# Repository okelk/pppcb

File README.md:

# pppcb

Sensor pcb for makersxchange Project 2021.

PPPCB is a ESP8266 development board with an integrated LED-Matrix and Piezo Preamplifier.

The board us currently still UNTESTED (as of 2021-02-25)

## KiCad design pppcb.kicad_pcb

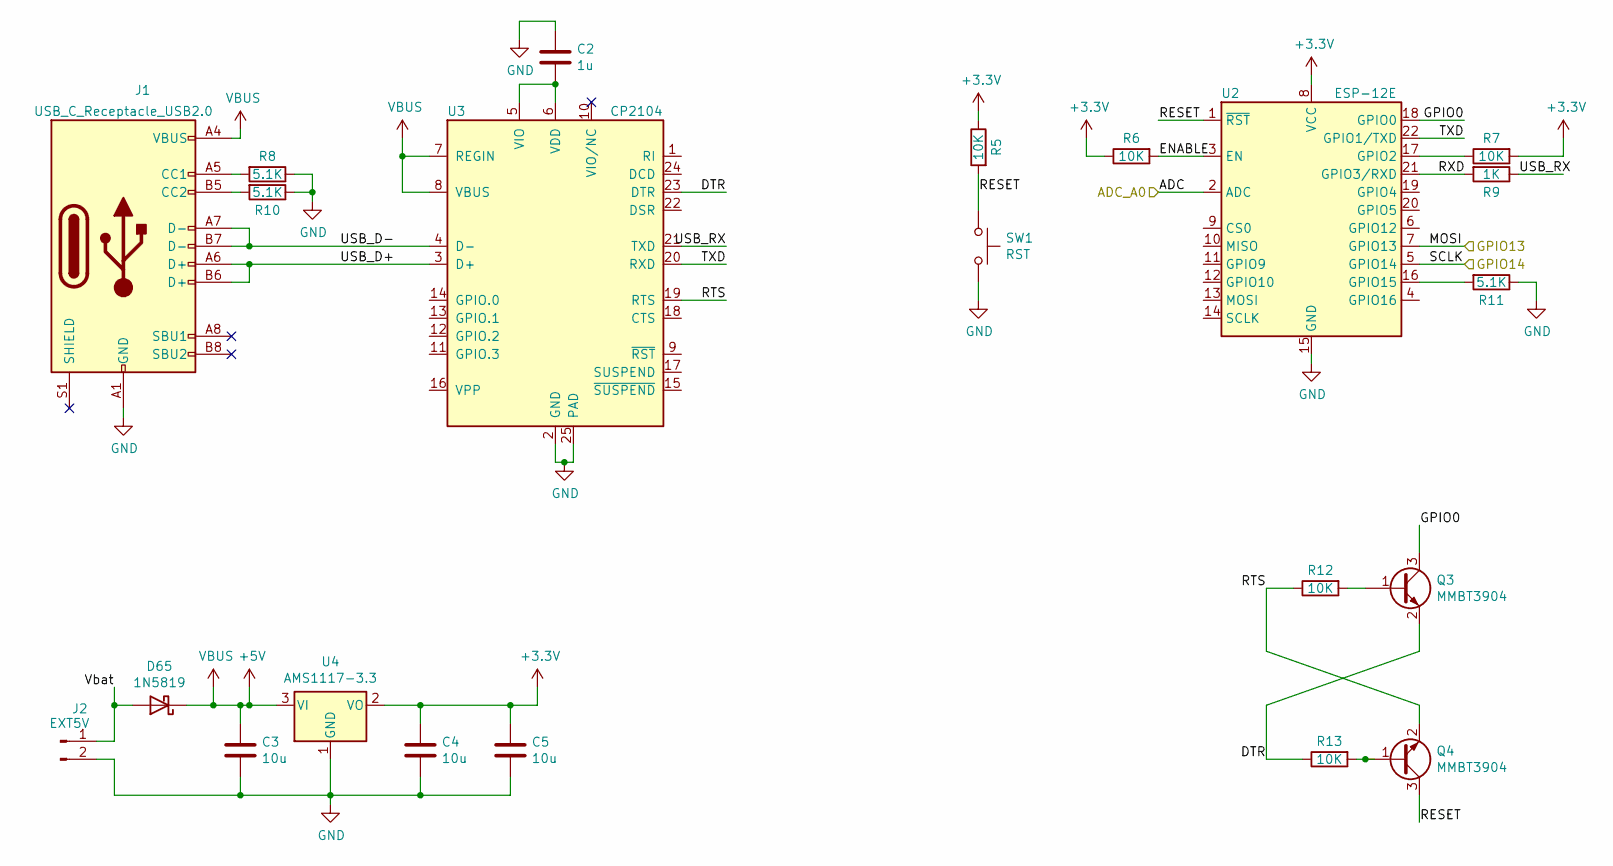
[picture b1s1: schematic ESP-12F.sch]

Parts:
C2: 1u; C_0603_1608Metric_Pad1.08x0.95mm_HandSolder
C3, C4, C5: 10u; C_0805_2012Metric
D65: 1N5819; D_DO-41_SOD81_P10.16mm_Horizontal
J1: USB_C_Receptacle_USB2.0; USB_C_Receptacle_HRO_TYPE-C-31-M-12
J2: EXT5V; PinHeader_1x02_P2.54mm_Horizontal
Q3, Q4: MMBT3904; SOT-23
R5, R6, R7, R12, R13: 10K; R_0603_1608Metric_Pad0.98x0.95mm_HandSolder
R8, R10, R11: 5.1K; R_0603_1608Metric_Pad0.98x0.95mm_HandSolder
R9: 1K; R_0603_1608Metric_Pad0.98x0.95mm_HandSolder
SW1: RST; Button_Tact_Sqkg
U2: ESP-12E
U3: CP2104; QFN-24-1EP_4x4mm_P0.5mm_EP2.6x2.6mm
U4: AMS1117-3.3; SOT-223-3_TabPin2

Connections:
+5V: C3.1, D65.1 (K), J1.A4 (VBUS), J1.A9 (VBUS), J1.B4 (VBUS), J1.B9 (VBUS), U3.7 (REGIN), U3.8 (VBUS), U4.3 (VI); also elsewhere on the board
/ESP-12F/ADC_A0: U2.2 (ADC); also elsewhere on the board
/ESP-12F/DTR: Q3.2 (E), R13.1, U3.23 (DTR)
/ESP-12F/ENABLE: R6.2, U2.3 (EN)
/ESP-12F/GPIO0: Q3.3 (C), U2.18 (GPIO0)
/ESP-12F/GPIO13: U2.7 (GPIO13); also elsewhere on the board
/ESP-12F/GPIO14: U2.5 (GPIO14); also elsewhere on the board
/ESP-12F/RESET: Q4.3 (C), R5.2, SW1.1, U2.1 (~RST)
/ESP-12F/RTS: Q4.2 (E), R12.1, U3.19 (RTS)
/ESP-12F/RXD: R9.2, U2.21 (GPIO3/RXD)
/ESP-12F/TXD: U2.22 (GPIO1/TXD), U3.20 (RXD)
/ESP-12F/USB_D+: J1.A6 (D+), J1.B6 (D+), U3.3 (D+)
/ESP-12F/USB_D-: J1.A7 (D-), J1.B7 (D-), U3.4 (D-)
/ESP-12F/USB_RX: R9.1, U3.21 (TXD)
/ESP-12F/Vbat: D65.2 (A), J2.1
GND: C2.1, C3.2, C4.2, C5.2, J1.A1 (GND), J1.A12 (GND), J1.B1 (GND), J1.B12 (GND), J2.2, R8.1, R10.1, R11.1, SW1.2, U2.15 (GND), U3.2 (GND), U3.25 (PAD), U4.1 (GND); also elsewhere on the board
unnamed: C2.2, U3.5 (VIO), U3.6 (VDD)
unnamed: J1.A5 (CC1), R8.2
unnamed: J1.B5 (CC2), R10.2
unnamed: Q3.1 (B), R12.2
unnamed: Q4.1 (B), R13.2
unnamed: R7.1, U2.17 (GPIO2)
unnamed: R11.2, U2.16 (GPIO15)

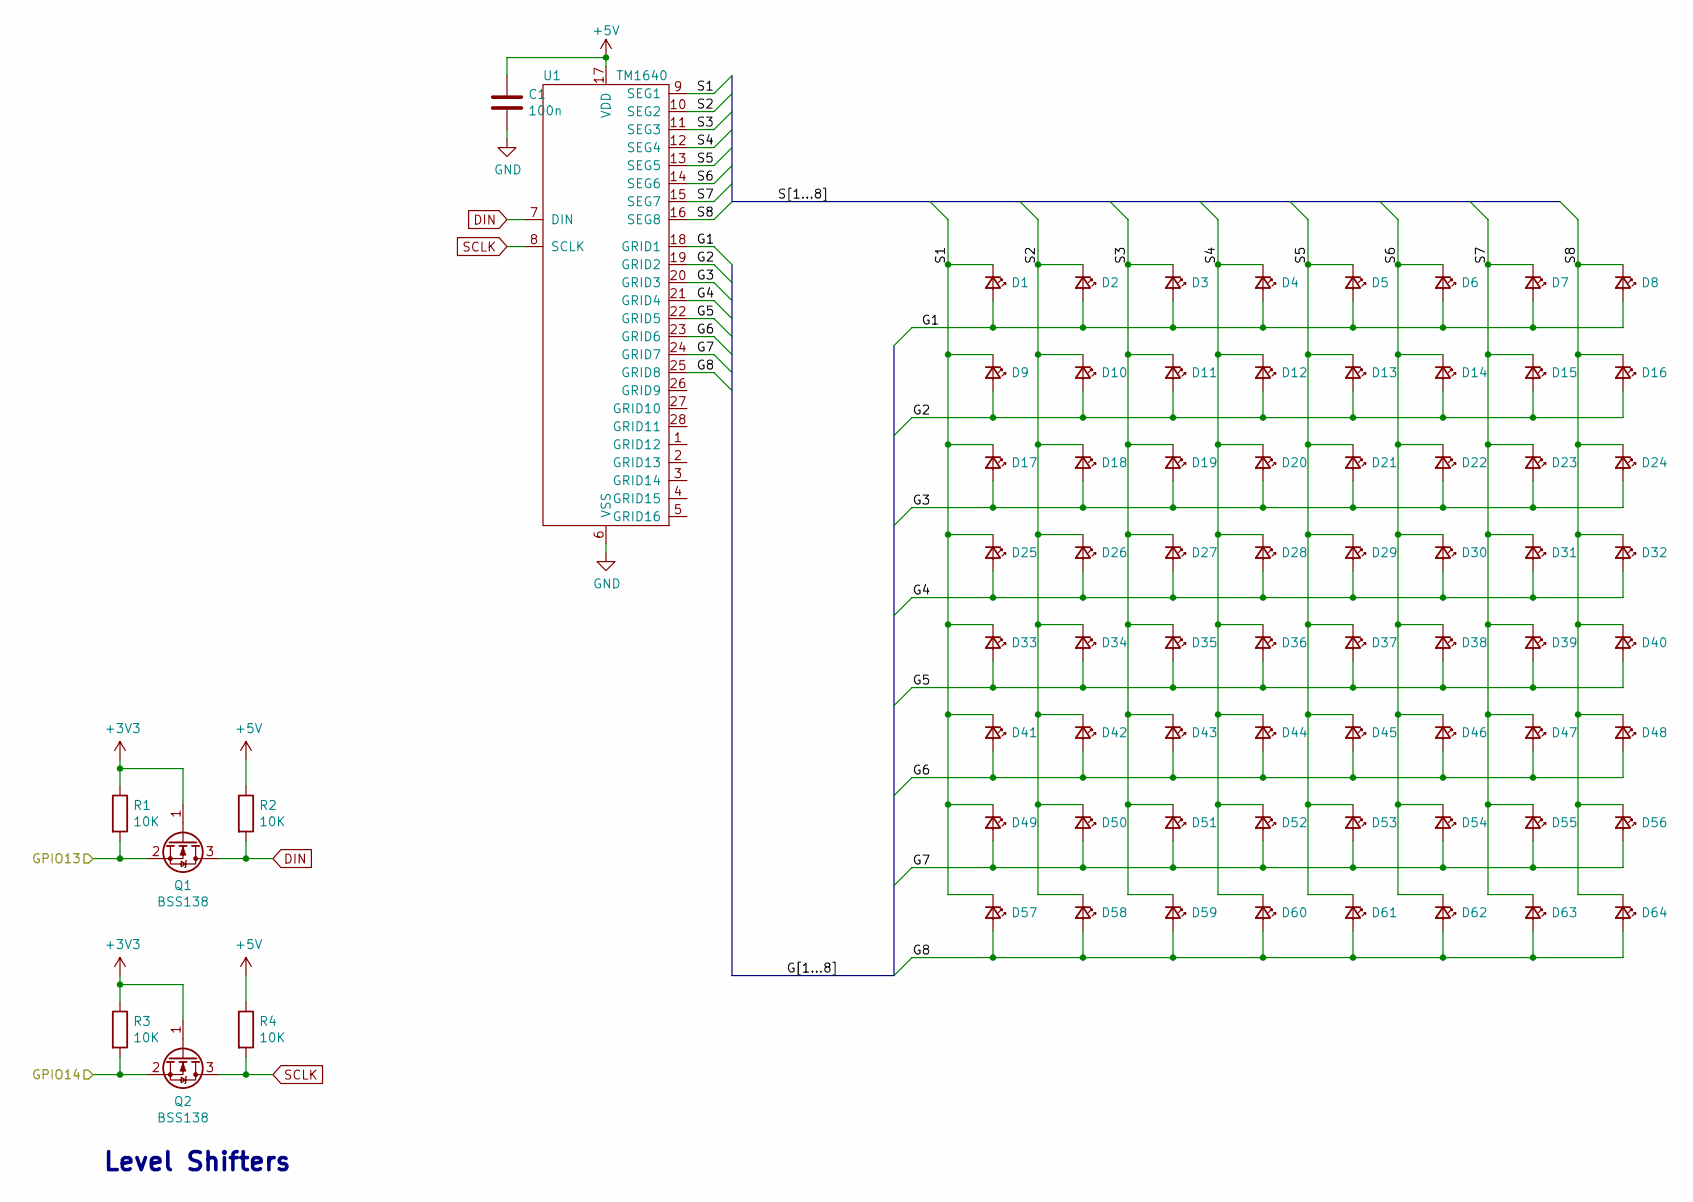
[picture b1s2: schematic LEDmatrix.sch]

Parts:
C1: 100n; C_0603_1608Metric_Pad1.08x0.95mm_HandSolder
D1, D2, D3, D4, D5, D6, D7, D8, D9, D10, D11, D12, D13, D14, D15, D16, D17, D18, D19, D20, D21, D22, D23, D24, D25, D26, D27, D28, D29, D30, D31, D32, D33, D34, D35, D36, D37, D38, D39, D40, D41, D42, D43, D44, D45, D46, D47, D48, D49, D50, D51, D52, D53, D54, D55, D56, D57, D58, D59, D60, D61, D62, D63, D64: LED_Small; LED_0603_1608Metric_Pad1.05x0.95mm_HandSolder
Q1, Q2: BSS138; SOT-23
R1, R2, R3, R4: 10K; R_0603_1608Metric_Pad0.98x0.95mm_HandSolder
U1: TM1640; SOIC-28W_7.5x18.7mm_P1.27mm

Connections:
+5V: C1.1, R2.1, R4.1, U1.17 (VDD); also elsewhere on the board
/ESP-12F/GPIO13: Q1.2 (S), R1.2; also elsewhere on the board
/ESP-12F/GPIO14: Q2.2 (S), R3.2; also elsewhere on the board
/LEDmatrix/G1: D1.2 (A), D2.2 (A), D3.2 (A), D4.2 (A), D5.2 (A), D6.2 (A), D7.2 (A), D8.2 (A), U1.18 (GRID1)
/LEDmatrix/G2: D9.2 (A), D10.2 (A), D11.2 (A), D12.2 (A), D13.2 (A), D14.2 (A), D15.2 (A), D16.2 (A), U1.19 (GRID2)
/LEDmatrix/G3: D17.2 (A), D18.2 (A), D19.2 (A), D20.2 (A), D21.2 (A), D22.2 (A), D23.2 (A), D24.2 (A), U1.20 (GRID3)
/LEDmatrix/G4: D25.2 (A), D26.2 (A), D27.2 (A), D28.2 (A), D29.2 (A), D30.2 (A), D31.2 (A), D32.2 (A), U1.21 (GRID4)
/LEDmatrix/G5: D33.2 (A), D34.2 (A), D35.2 (A), D36.2 (A), D37.2 (A), D38.2 (A), D39.2 (A), D40.2 (A), U1.22 (GRID5)
/LEDmatrix/G6: D41.2 (A), D42.2 (A), D43.2 (A), D44.2 (A), D45.2 (A), D46.2 (A), D47.2 (A), D48.2 (A), U1.23 (GRID6)
/LEDmatrix/G7: D49.2 (A), D50.2 (A), D51.2 (A), D52.2 (A), D53.2 (A), D54.2 (A), D55.2 (A), D56.2 (A), U1.24 (GRID7)
/LEDmatrix/G8: D57.2 (A), D58.2 (A), D59.2 (A), D60.2 (A), D61.2 (A), D62.2 (A), D63.2 (A), D64.2 (A), U1.25 (GRID8)
/LEDmatrix/S1: D1.1 (K), D9.1 (K), D17.1 (K), D25.1 (K), D33.1 (K), D41.1 (K), D49.1 (K), D57.1 (K), U1.9 (SEG1)
/LEDmatrix/S2: D2.1 (K), D10.1 (K), D18.1 (K), D26.1 (K), D34.1 (K), D42.1 (K), D50.1 (K), D58.1 (K), U1.10 (SEG2)
/LEDmatrix/S3: D3.1 (K), D11.1 (K), D19.1 (K), D27.1 (K), D35.1 (K), D43.1 (K), D51.1 (K), D59.1 (K), U1.11 (SEG3)
/LEDmatrix/S4: D4.1 (K), D12.1 (K), D20.1 (K), D28.1 (K), D36.1 (K), D44.1 (K), D52.1 (K), D60.1 (K), U1.12 (SEG4)
/LEDmatrix/S5: D5.1 (K), D13.1 (K), D21.1 (K), D29.1 (K), D37.1 (K), D45.1 (K), D53.1 (K), D61.1 (K), U1.13 (SEG5)
/LEDmatrix/S6: D6.1 (K), D14.1 (K), D22.1 (K), D30.1 (K), D38.1 (K), D46.1 (K), D54.1 (K), D62.1 (K), U1.14 (SEG6)
/LEDmatrix/S7: D7.1 (K), D15.1 (K), D23.1 (K), D31.1 (K), D39.1 (K), D47.1 (K), D55.1 (K), D63.1 (K), U1.15 (SEG7)
/LEDmatrix/S8: D8.1 (K), D16.1 (K), D24.1 (K), D32.1 (K), D40.1 (K), D48.1 (K), D56.1 (K), D64.1 (K), U1.16 (SEG8)
DIN: Q1.3 (D), R2.2, U1.7 (DIN)
GND: C1.2, U1.6 (VSS); also elsewhere on the board
SCLK: Q2.3 (D), R4.2, U1.8 (SCLK)

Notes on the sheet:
Level Shifters

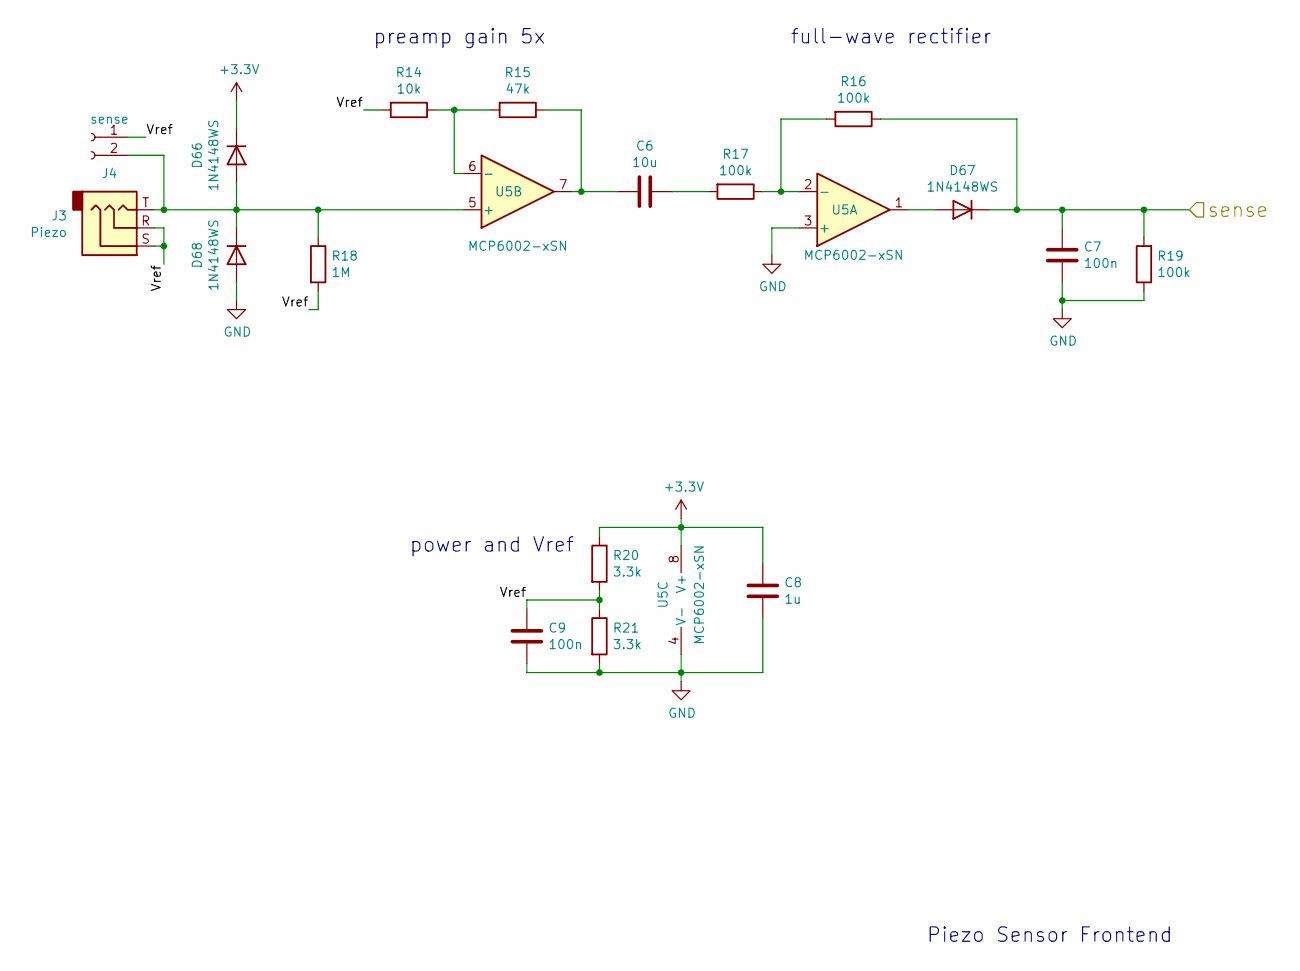
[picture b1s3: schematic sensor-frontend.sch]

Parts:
C6: 10u; C_0805_2012Metric
C7, C9: 100n; C_0603_1608Metric_Pad1.08x0.95mm_HandSolder
C8: 1u; C_0603_1608Metric_Pad1.08x0.95mm_HandSolder
D66, D67, D68: 1N4148WS; D_SOD-323
J3: Piezo; Jack_3.5mm_PJ320D_Horizontal
J4: sense; PinSocket_1x02_P2.54mm_Vertical
R14: 10k; R_0603_1608Metric_Pad0.98x0.95mm_HandSolder
R15: 47k; R_0603_1608Metric_Pad0.98x0.95mm_HandSolder
R16, R17, R19: 100k; R_0603_1608Metric_Pad0.98x0.95mm_HandSolder
R18: 1M; R_0603_1608Metric_Pad0.98x0.95mm_HandSolder
R20, R21: 3.3k; R_0603_1608Metric_Pad0.98x0.95mm_HandSolder
U5: MCP6002-xSN; SOIC-8_3.9x4.9mm_P1.27mm

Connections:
/ESP-12F/ADC_A0: C7.1, D67.1 (K), R16.1, R19.2; also elsewhere on the board
/Sensor/Vref: C9.1, J3.R, J3.S, J4.1, R14.2, R18.2, R20.2, R21.1
GND: C7.2, C8.2, C9.2, D68.2 (A), R19.1, R21.2, U5.3 (+), U5.4 (V-); also elsewhere on the board
unnamed: C6.1, R17.2
unnamed: C6.2, R15.1, U5.7
unnamed: D66.2 (A), D68.1 (K), J3.T, J4.2, R18.1, U5.5 (+)
unnamed: D67.2 (A), U5.1
unnamed: R14.1, R15.2, U5.6 (-)
unnamed: R16.2, R17.1, U5.2 (-)

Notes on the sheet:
Piezo Sensor Frontend
power and Vref
preamp gain 5x
full-wave rectifier

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
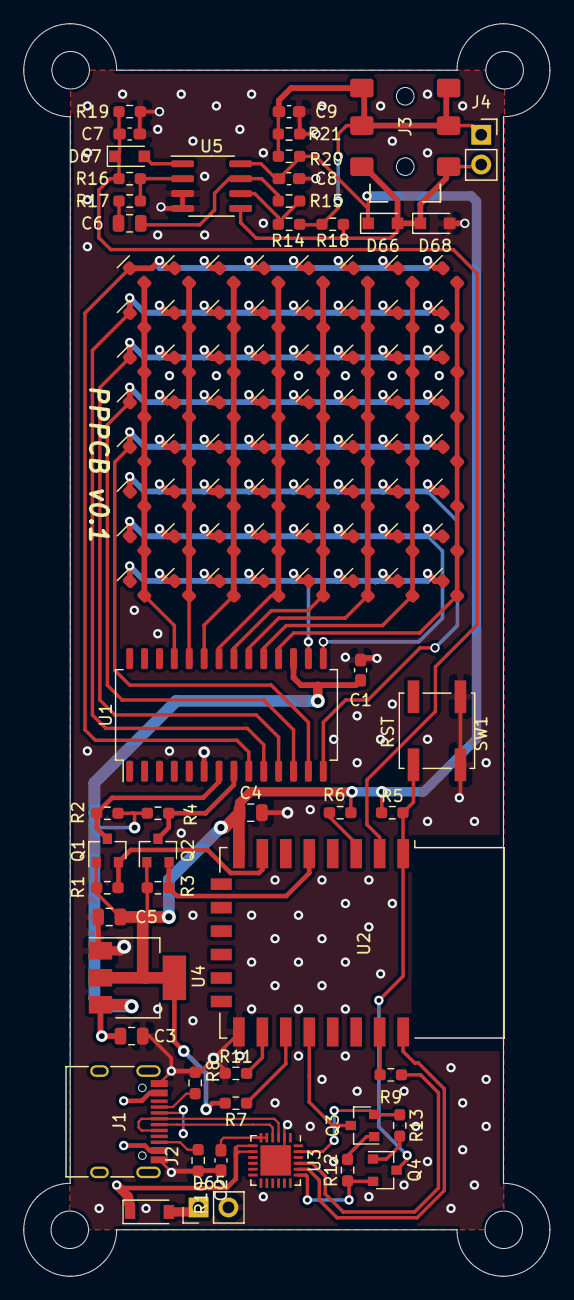
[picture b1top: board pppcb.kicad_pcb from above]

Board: 2 copper layers, 44.9 x 106.8 mm, 112 parts (0 on the bottom side), 49 nets.

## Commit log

2021-02-16 unifinished
2021-02-25 v0.1
